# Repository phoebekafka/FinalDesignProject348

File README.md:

# EE_348_StudentFiles_FinalProj
These are final Project Files and Templates for students to use for the 348 class at USC. This class goes over the basics of Analog Design and this project is meany to introduce students to their first amplifier design.

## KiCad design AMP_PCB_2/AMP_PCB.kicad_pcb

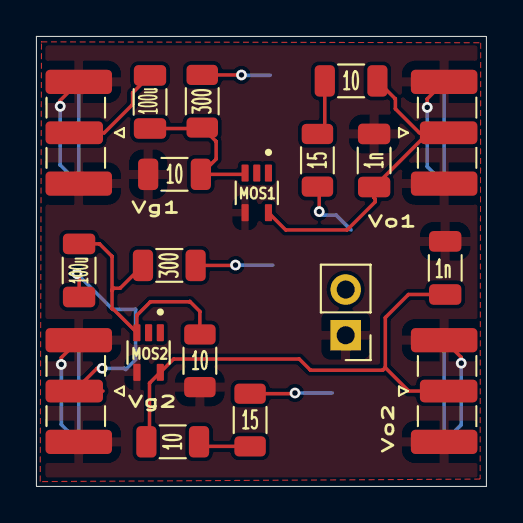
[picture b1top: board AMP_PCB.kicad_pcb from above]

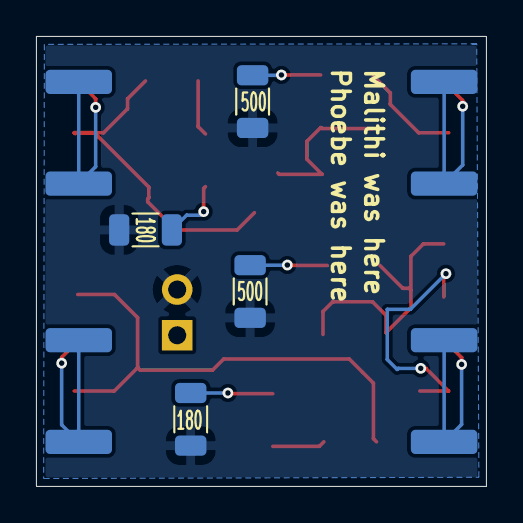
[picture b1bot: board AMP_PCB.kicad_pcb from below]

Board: 2 copper layers, 25.0 x 25.0 mm, 23 parts (4 on the bottom side), 14 nets.

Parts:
180: 180Ω; R_1206_3216Metric
C1, C2: 1n; C_1206_3216Metric
C3, C4: 100u; C_1206_3216Metric
J1, J2: Conn_Coaxial; SMA_Samtec_SMA-J-P-H-ST-EM1_EdgeMount
J5: Conn_01x02_Pin; PinHeader_1x02_P2.54mm_Vertical
MOS1, MOS2: JFE150DCKR; TRANS_JFE150DCKR
R1, R2: 15; R_1206_3216Metric
R3, R4, R7, R8: 10; R_1206_3216Metric
R5, R6: 300; R_1206_3216Metric
R9: 180; R_1206_3216Metric
R11, R12: 500; R_1206_3216Metric
Vo1, Vo2: Conn_Coaxial; SMA_Samtec_SMA-J-P-H-ST-EM1_EdgeMount

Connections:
/Vout1: C1.2, MOS1.5 (D), R3.2, Vo1.1 (In)
/Vout2: C2.2, MOS2.5 (D), R4.2, Vo2.1 (In)
GND: C1.1, C2.1, J1.2 (Ext), J2.2 (Ext), J5.1, MOS1.4 (S), MOS2.4 (S), R7.2, R8.2, Vo1.2 (Ext), Vo2.2 (Ext)
unnamed: C3.1, MOS1.3 (G), R5.2, R7.1
unnamed: C4.2, MOS2.3 (G), R6.2, R8.1
unnamed: R1.1, R9.2
unnamed: R1.2, R3.1
unnamed: R2.2, R4.1
unnamed: 180.2, R2.1
unnamed: R5.1, R11.2
unnamed: R6.1, R12.2
Vdd: 180.1, J5.2, R9.1, R11.1, R12.1
Vgate1: C3.2, J1.1 (In)
Vgate2: C4.1, J2.1 (In)

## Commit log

2025-11-11 malithi's og version
2025-11-12 updated schematic with OP
2025-11-12 Little changes to AMP schematic
2025-11-12 pray:
2025-11-12 updated footprint ver
2025-11-13 updated design + footprints
2025-11-13 traces and pcb
